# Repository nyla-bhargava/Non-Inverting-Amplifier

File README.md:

# Non-Inverting-Amplifier
This repository contains the complete project files for designing and laying out a Non-Inverting Amplifier circuit PCB using KiCad.

# 📋 Project Overview

This project focuses on creating a simple operational amplifier (op-amp) based non-inverting amplifier circuit, designing the schematic, and developing a ready-for-manufacturing PCB.
It's perfect for beginners and electronics enthusiasts learning PCB design workflows with KiCad.

# 🛠️ Tools Used

   KiCad (Version 7.x recommended)

   Basic understanding of operational amplifiers and PCB design principles.
   
# 📂 Repository Structure

| File/Folder | Purpose |
|:-----------|:--------|
| `NonInvertingAmp.pro` | Main KiCad project file that links everything together. |
| `NonInvertingAmp.sch` | KiCad schematic file containing the amplifier circuit diagram. |
| `NonInvertingAmp.kicad_pcb` | PCB layout file for the circuit (component placement, routing, etc.). |

---

## 🧩 Circuit Description

The **non-inverting amplifier** circuit configuration provides a **positive voltage gain** without inverting the input signal.  
It uses a standard operational amplifier (e.g., **LM741**, **TL081**, or similar) and a pair of resistors to set the gain.

The gain formula:

\[
Gain = 1 + \left( \frac{R_f}{R_{in}} \right)
\]

where:  
- \( R_f \) = feedback resistor  
- \( R_{in} \) = input resistor

---

## 🚀 How to Use

1. Clone or download the repository.
2. Open `NonInvertingAmplifier.pro` in KiCad.
3. Explore the schematic (`.sch`) to understand and modify the design if needed.
4. Open the PCB layout (`.kicad_pcb`) to view or edit the board.
5. Use KiCad's **Plot** tool to regenerate Gerber files if you make changes.
6. Order your PCB using the `gerber/` files!

---

## 📸 Previews

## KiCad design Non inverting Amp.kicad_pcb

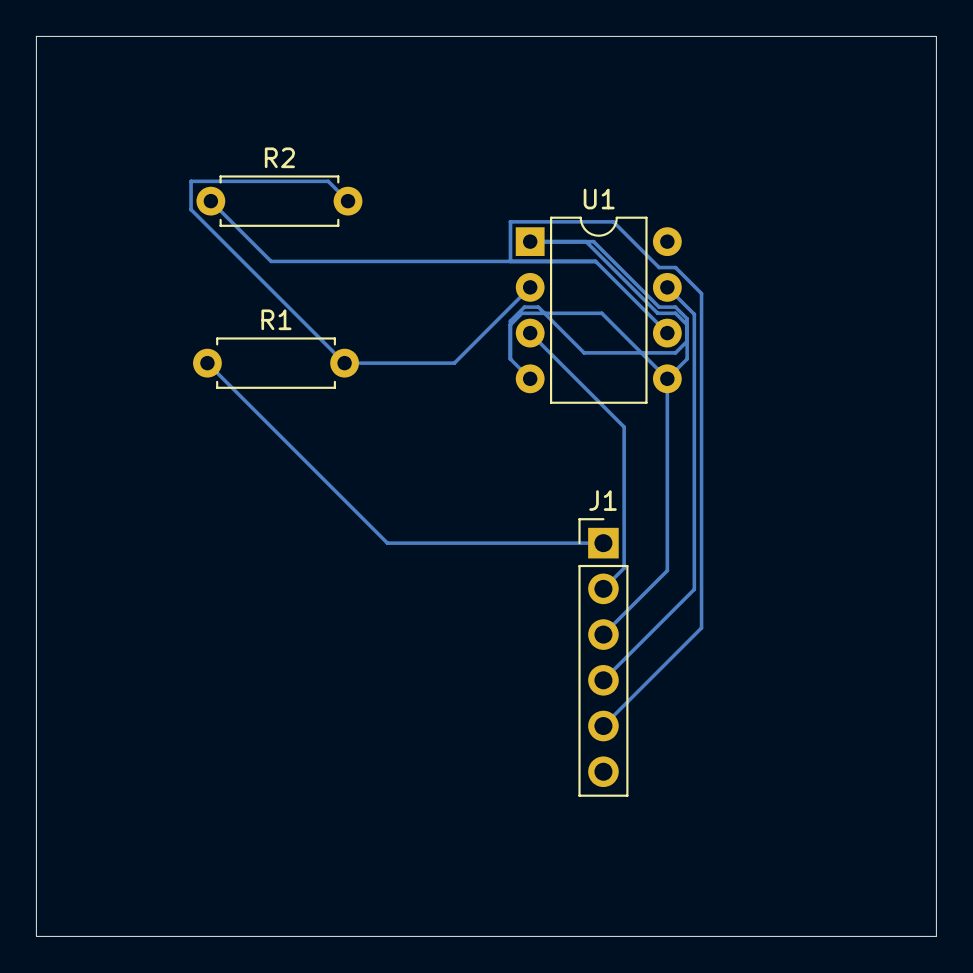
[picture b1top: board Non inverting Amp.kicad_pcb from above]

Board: 2 copper layers, 50.0 x 50.0 mm, 4 parts (0 on the bottom side), 5 nets.

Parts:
J1: Conn_01x06_Pin; PinHeader_1x06_P2.54mm_Vertical
R1: 1kΩ; R_Axial_DIN0207_L6.3mm_D2.5mm_P7.62mm_Horizontal
R2: 50kΩ; R_Axial_DIN0207_L6.3mm_D2.5mm_P7.62mm_Horizontal
U1: LM741; DIP-8_W7.62mm

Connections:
unnamed: J1.1, R1.1
unnamed: J1.2, U1.3 (+)
unnamed: J1.4, U1.7 (V+)
unnamed: J1.5, R2.1, U1.6
unnamed: R1.2, R2.2, U1.2 (-)
